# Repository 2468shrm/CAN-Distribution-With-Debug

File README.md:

# CAN-Distribution-With-Debug

## Board Layout

## Disclaimer
This board has not been fabricated or tested. It is to be considered
alpha and subject to bugs and errors. Use at your own risk. However the Gerbers
are provided should you want to fabricate your own.

The board is designed with KiCAD, the schematic and PCB files are included.

## Enclosure

An 3D-printable enclosure is avaiable for this board. [Enclosure link](https://github.com/2468shrm/CAN-Distribution-Board-Enclosure)

## Introduction
This is a board created to simplify CAN wiring on FRC robots. It was created by the
mentors of FRC2468/2687/2689.

### Board Schematic

The PDF of the schematic is available at this [schematic link](https://github.com/2468shrm/CAN-Distribution-With-Debug/blob/main/Images/Schematic.pdf)

### Features

The board has 5 CAN connections and 3 power connections. The intended use is for
the CAN connections of either a swerve module or a WCD gearbox.
- Power
  - One connection upstream
  - One connection downstream
  - One connection to a local sensor (e.g. a CANcoder)
- CAN
  - One connection upstream
  - One connection downstream
  - One connection to a drive motor controller (Falcon 500, SPARK MAX)
  - One connection to a drive or steering motor
  - One connection to a CAN-connected sensor (CANcoder)

## CAN and Power Connections
The connectors for the CAN and power are WAGO 250-204s (X1, X2, X3, X4).

## Termination
The board contains a 2x2 header (J1) to allow for jumpers to be installed to enable
CAN termination.
- No jumpers means no termination
- One jumper provides 120 ohms termination (single end termination)
- Two jumpers provides 60 ohms termination (full termination)

Populating the termination circuitry is optional.

## Debug
This board also has some experimental CAN debug features. It contains a small power
supply module, a CAN transceiver, and an LED.

The LED is intended to show CAN traffic. It should flicker during traffic; although
the light may just be different intensities and not discrete flickers.

The CAN transceiver is configured in silent mode and the transmit is wired high to
ensure the transceiver is in tristate (recessive).

There are also two test points on the CAN_H and CAN_L signals.

Populating the debug circuitry is optional.

# 3D Views of the Board
## Top

## Iso Front

## Iso Back

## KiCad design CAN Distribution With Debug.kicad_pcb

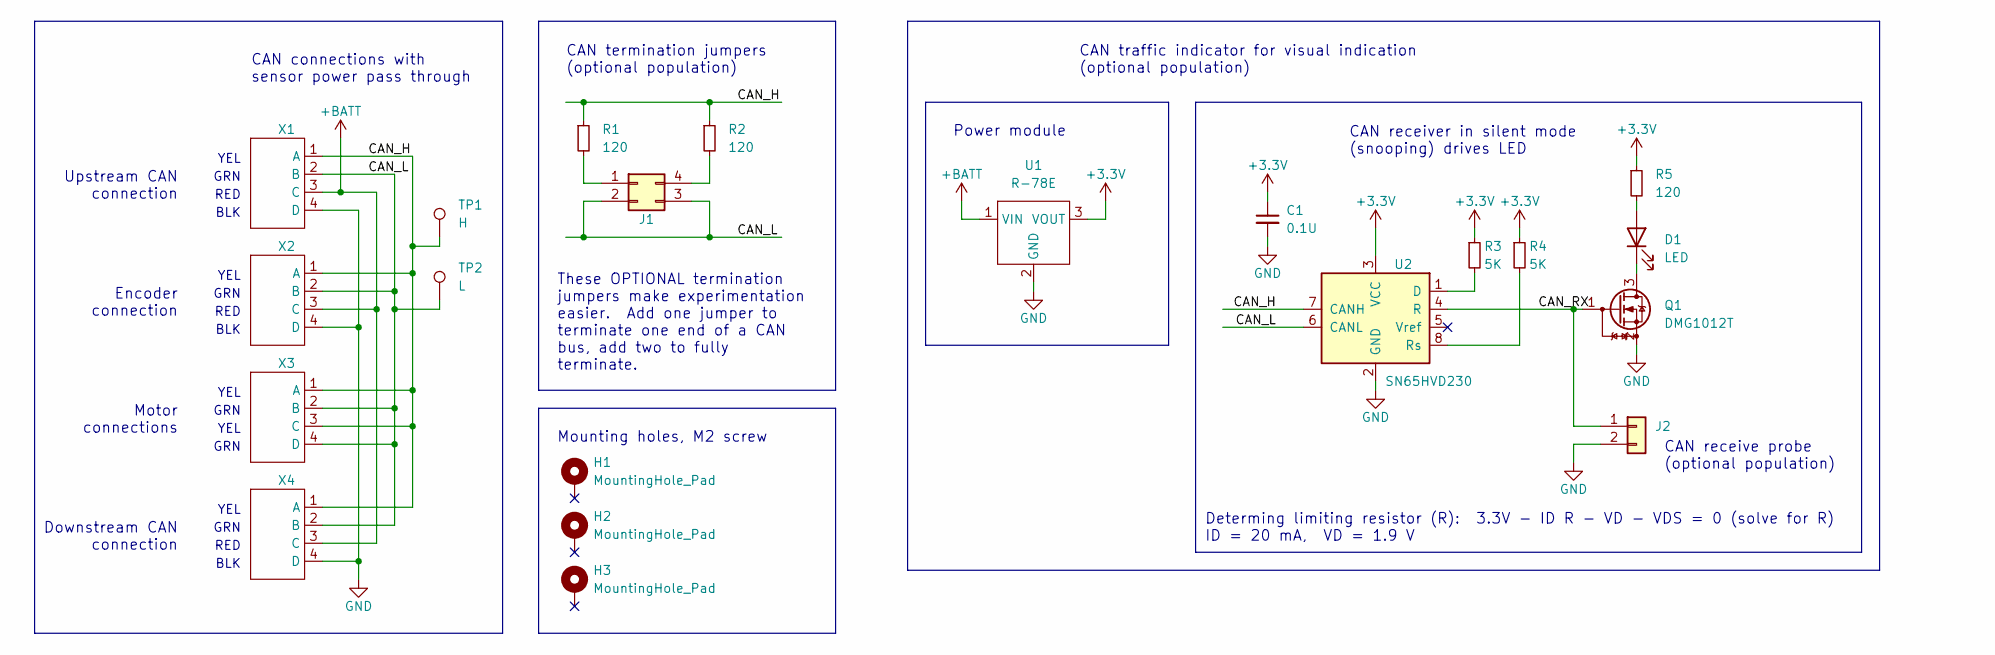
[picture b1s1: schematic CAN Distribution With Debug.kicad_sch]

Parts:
C1: 0.1U; C_0805_2012Metric
D1: LED; LED_1206_3216Metric
H1, H2, H3: MountingHole_Pad; MountingHole_2.2mm_M2_Pad
J1: Conn_02x02_Counter_Clockwise; PinHeader_2x02_P2.54mm_Vertical
J2: Conn_01x02; PinHeader_1x02_P2.54mm_Vertical
Q1: DMG1012T; SOT-523
R1, R2, R5: 120; R_0805_2012Metric
R3, R4: 5K; R_0805_2012Metric
TP1: H; TestPoint_Pad_D1.5mm
TP2: L; TestPoint_Pad_D1.5mm
U1: R-78E
U2: SN65HVD230; SOIC-8_3.9x4.9mm_P1.27mm
X1, X2, X3, X4: WAGO_250-204; WAGO 250-204

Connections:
+3.3V: C1.1, R3.1, R4.1, R5.1, U1.3 (VOUT), U2.3 (VCC)
+BATT: U1.1 (VIN), X1.3 (C), X2.3 (C), X4.3 (C)
/CAN_H: R1.1, R2.1, TP1.1, U2.7 (CANH), X1.1 (A), X2.1 (A), X3.1 (A), X3.3 (C), X4.1 (A)
/CAN_L: J1.2, J1.3, TP2.1, U2.6 (CANL), X1.2 (B), X2.2 (B), X3.2 (B), X3.4 (D), X4.2 (B)
/CAN_RX: J2.1, Q1.1 (G), U2.4 (R)
GND: C1.2, J2.2, Q1.2 (S), U1.2 (GND), U2.2 (GND), X1.4 (D), X2.4 (D), X4.4 (D)
unnamed: D1.1 (K), Q1.3 (D)
unnamed: D1.2 (A), R5.2
unnamed: J1.1, R1.2
unnamed: J1.4, R2.2
unnamed: R3.2, U2.1 (D)
unnamed: R4.2, U2.8 (Rs)

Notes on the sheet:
BLK
GRN
CAN receive probe (optional population)
YEL
CAN termination jumpers (optional population)
Encoder connection
CAN receiver in silent mode (snooping) drives LED
Determing limiting resistor (R): 3.3V - ID R - VD - VDS = 0 (solve for R) ID = 20 mA, VD = 1.9 V
RED
Upstream CAN connection
CAN traffic indicator for visual indication (optional population)
Mounting holes, M2 screw
These OPTIONAL termination jumpers make experimentation easier. Add one jumper to terminate one end of a CAN bus, add two to fully terminate.
CAN connections with sensor power pass through
Power module
Motor connections
Downstream CAN connection

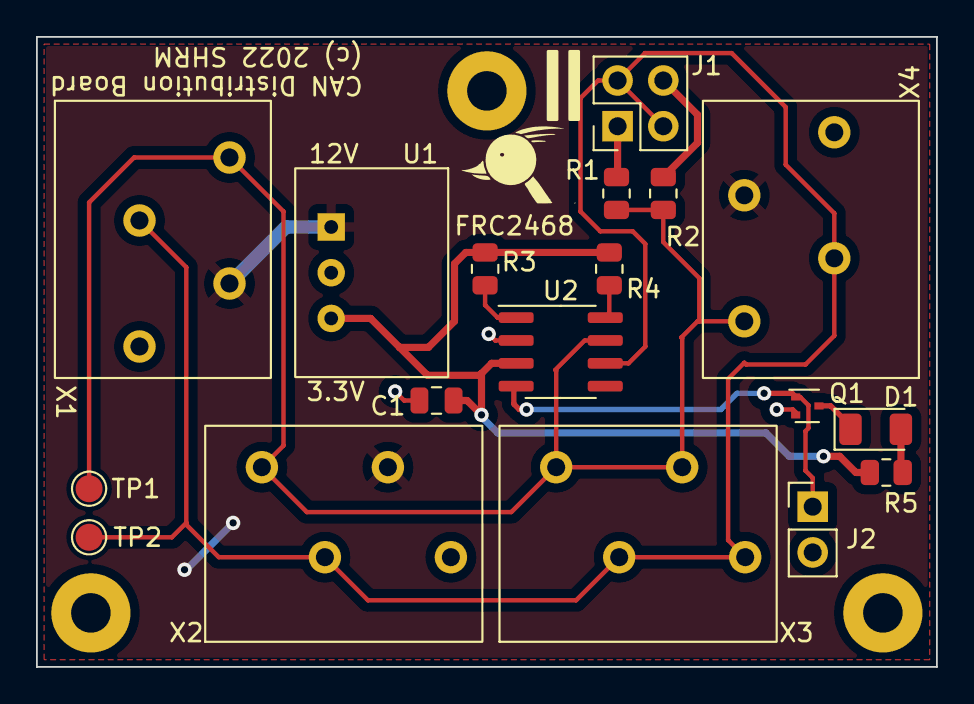
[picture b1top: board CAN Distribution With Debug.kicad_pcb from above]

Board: 2 copper layers, 50.0 x 35.0 mm, 21 parts (0 on the bottom side), 12 nets.

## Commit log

2022-12-26 initial design files
2022-12-26 updated README (renders)
2023-01-06 added enclosure link to README
2023-01-06 added Gerber ZIP file
2023-01-06 removed backup file
2023-01-06 added schematic image
2023-01-06 added schematic PNG
2023-01-06 updated README with schematic info
2023-01-07 removing Gerbers.zip
2023-01-07 updated Gerbers.zip (added back)

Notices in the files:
CAN Distribution With Debug.kicad_pcb:
(c) 2022 SHRM
